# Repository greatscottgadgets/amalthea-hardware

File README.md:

# amalthea-hardware

Amalthea is an experimental experimental SDR platform implemented as a mezzanine add-on for [Cynthion](https://greatscottgadgets.com/cynthion/).

Gateware and host software may be found in the [amalthea repository](https://github.com/greatscottgadgets/amalthea).

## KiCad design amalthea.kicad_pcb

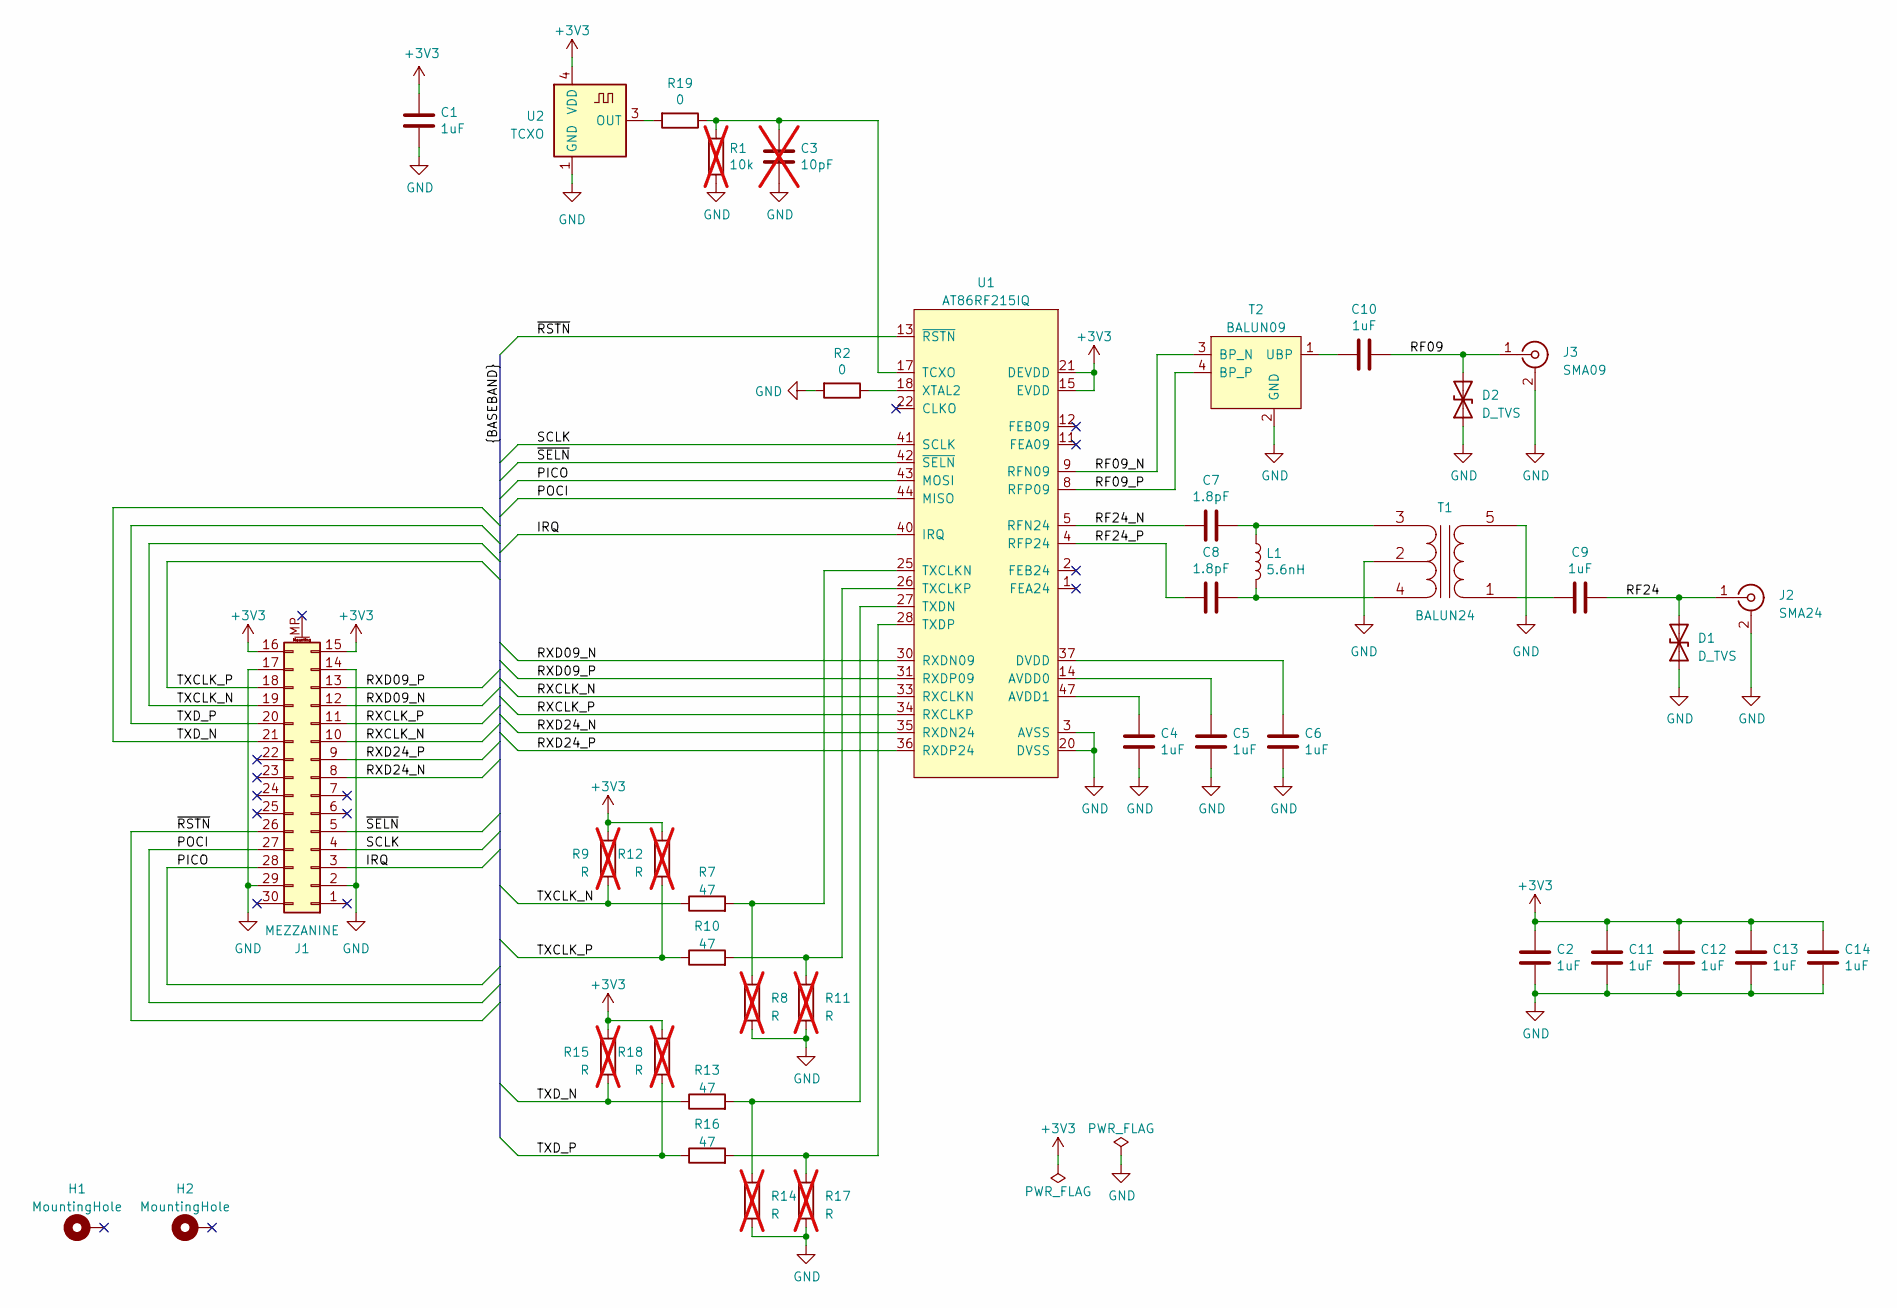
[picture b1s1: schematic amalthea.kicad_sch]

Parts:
C1, C2, C4, C5, C6, C9, C10, C11, C12, C13, C14: 1uF; C_0402_1005Metric; Manufacturer Part Number CL05A105KA5NQNC; JLCPCB Part Number C52923
C3: 10pF; C_0402_1005Metric; not fitted
C7, C8: 1.8pF; C_0402_1005Metric; Manufacturer Part Number GJM1555C1H1R8BB01D; JLCPCB Part Number C76902
D1, D2: D_TVS; DFN1006-2; Manufacturer Part Number ESDSLC5V0LBS; JLCPCB Part Number C2762105
H1, H2: MountingHole; MountingHole_2.2mm_M2_Pad_Via
J1: MEZZANINE; Amphenol_10132797-03; Manufacturer Part Number 10132797-033100LF; JLCPCB Part Number n/a
J2: SMA24; SMA-EDGE; Manufacturer Part Number CONSMA003.062; JLCPCB Part Number n/a
J3: SMA09; SMA-EDGE; Manufacturer Part Number CONSMA003.062; JLCPCB Part Number n/a
L1: 5.6nH; L_0402_1005Metric; Manufacturer Part Number MLG1005S5N6CT000; JLCPCB Part Number C275295
R1: 10k; R_0402_1005Metric; not fitted
R2, R19: 0; R_0402_1005Metric; Manufacturer Part Number 0402WGF0000TCE; JLCPCB Part Number C17168
R7, R10, R13, R16: 47; R_0402_1005Metric; Manufacturer Part Number 0402WGF470JTCE; JLCPCB Part Number C25118
R8, R9, R11, R12, R14, R15, R17, R18: R; R_0402_1005Metric; not fitted
T1: BALUN24; Balun_Johanson_0896BM15A0001; Manufacturer Part Number 2450FB15A050; JLCPCB Part Number C5244324
T2: BALUN09; Balun_Johanson_0896BM15A0001; Manufacturer Part Number 0896BM15E0025; JLCPCB Part Number C3304914
U1: AT86RF215IQ; QFN-48-1EP_7x7mm_P0.5mm_EP5.6x5.6mm_ThermalVias; Manufacturer Part Number AT86RF215IQ-ZU; JLCPCB Part Number C1558327
U2: TCXO; Crystal_SMD_2016-4Pin_2.0x1.6mm; Manufacturer Part Number 6TG2600001; JLCPCB Part Number C5121629

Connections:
+3V3: C1.1, C2.1, C11.1, C12.1, C13.1, C14.1, J1.15, J1.16, R9.2, R12.2, R15.2, R18.2, U1.15 (EVDD), U1.21 (DEVDD), U1.29 (DEVDD), U1.39 (DEVDD), U1.46 (EVDD), U2.4 (VDD)
/IRQ: J1.3, U1.40 (IRQ)
/PICO: J1.28, U1.43 (MOSI)
/POCI: J1.27, U1.44 (MISO)
/RF09: C10.1, D2.2 (A2), J3.1 (In)
/RF09_N: T2.3 (BP_N), U1.9 (RFN09)
/RF09_P: T2.4 (BP_P), U1.8 (RFP09)
/RF24: C9.1, D1.2 (A2), J2.1 (In)
/RF24_N: C7.2, U1.5 (RFN24)
/RF24_P: C8.1, U1.4 (RFP24)
/RXCLK_N: J1.10, U1.33 (RXCLKN)
/RXCLK_P: J1.11, U1.34 (RXCLKP)
/RXD09_N: J1.12, U1.30 (RXDN09)
/RXD09_P: J1.13, U1.31 (RXDP09)
/RXD24_N: J1.8, U1.35 (RXDN24)
/RXD24_P: J1.9, U1.36 (RXDP24)
/SCLK: J1.4, U1.41 (SCLK)
/TXCLK_N: J1.19, R7.1, R9.1
/TXCLK_P: J1.18, R10.1, R12.1
/TXD_N: J1.21, R13.1, R15.1
/TXD_P: J1.20, R16.1, R18.1
/~RSTN: J1.26, U1.13 (~RSTN)
/~SELN: J1.5, U1.42 (~SELN)
GND: C1.2, C2.2, C3.2, C4.2, C5.2, C6.2, C11.2, C12.2, C13.2, C14.2, D1.1 (A1), D2.1 (A1), J1.2, J1.14, J1.17, J1.29, J2.2 (Ext), J3.2 (Ext), R1.2, R2.2, R8.1, R11.1, R14.1, R17.1, T1.2 (PM), T1.5 (S2), T2.2 (GND), T2.5 (GND), T2.6 (GND), U1.3 (AVSS), U1.6 (AVSS), U1.7 (AVSS), U1.10 (AVSS), U1.16 (AVSS), U1.19 (AVSS), U1.20 (DVSS), U1.23 (DVSS), U1.24 (DVSS), U1.32 (DVSS), U1.38 (DVSS), U1.45 (AVSS), U1.48 (AVSS), U1.49 (AVSS), U2.1 (GND), U2.2 (GND)
unnamed: C7.1, L1.1, T1.3 (PR1)
unnamed: C8.2, L1.2, T1.4 (PR2)
unnamed: C9.2, T1.1 (S1)
unnamed: C10.2, T2.1 (UBP)
unnamed: C5.1, U1.14 (AVDD0)
unnamed: C4.1, U1.47 (AVDD1)
unnamed: C6.1, U1.37 (DVDD)
unnamed: C3.1, R1.1, R19.1, U1.17 (TCXO)
unnamed: R7.2, R8.2, U1.25 (TXCLKN)
unnamed: R10.2, R11.2, U1.26 (TXCLKP)
unnamed: R13.2, R14.2, U1.27 (TXDN)
unnamed: R16.2, R17.2, U1.28 (TXDP)
unnamed: R2.1, U1.18 (XTAL2)
unnamed: R19.2, U2.3 (OUT)

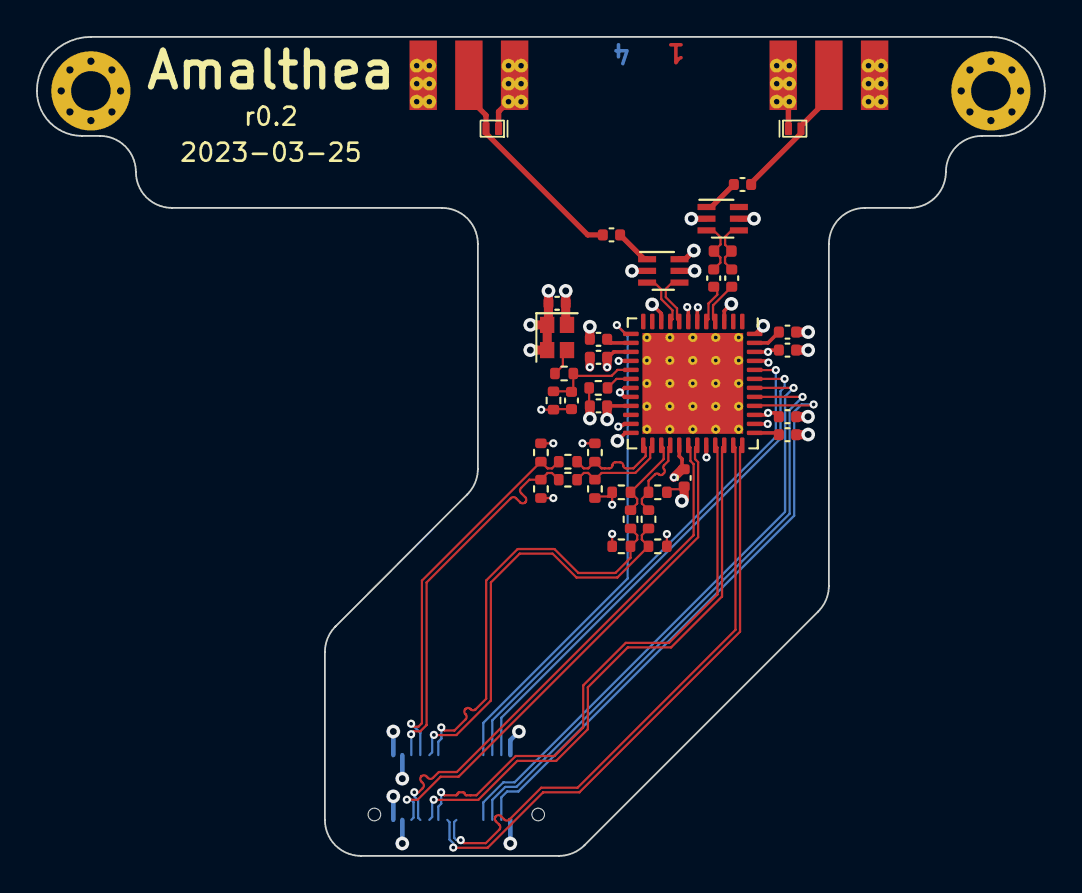
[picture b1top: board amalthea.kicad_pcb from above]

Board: 4 copper layers, 56.0 x 45.5 mm, 41 parts (1 on the bottom side), 38 nets.

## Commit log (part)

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2023-03-27 add Amalthea r0.2 design files and license
    The Amalthea r0.1 hardware design was located in the amalthea
    gateware/software repository. Going forward, hardware will be in this
    separate repository.
    Amalthea r0.1 was a complete board with FPGA while r0.2 is implemented
    as a mezzanine add-on for Cynthion.

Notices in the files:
amalthea.kicad_pcb:
Copyright 2020-2023 Great Scott Gadgets
Licensed under the CERN-OHL-P v2
